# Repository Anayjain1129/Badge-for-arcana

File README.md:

# Badge-for-arcana
A PCB badge for horizons arcana! 

# Schematics 

# PCB

# Why did i made this?
I was just trying to try new projects and learn more about hardware projects.

# Features:-
- could be used as a arcana badge
- Awesome silkscreen
- uses 555 timer
- Cool Leds

# BOM 
| #  | Component                       |   Qty | Unit Price (USD) | Total (USD) |
| -- | ------------------------------- | ----: | ---------------: | ----------: |
| 1  | 555 Timer IC (NE555)            |     1 |            $0.20 |       $0.20 |
| 2  | CR2032 Coin Cell Battery        |     2 |            $0.35 |       $0.70 |
| 3  | CR2032 Coin Cell Battery Holder |     2 |            $0.15 |       $0.30 |
| 4  | 5mm LED                         |     6 |            $0.05 |       $0.30 |
| 5  | 270Ω Resistor                   |     6 |            $0.01 |       $0.06 |
| 6  | 10kΩ Resistor                   |     1 |            $0.01 |       $0.01 |
| 7  | 1kΩ Resistor                    |     1 |            $0.01 |       $0.01 |
| 8  | 100µF Capacitor                 |     1 |            $0.08 |       $0.08 |
| 9  | 6mm Push Button                 |     1 |            $0.05 |       $0.05 |
| 10 | **PCB**                         | **1** |        **$5.00** |   **$5.00** |
|    | **Total**                       |       |                  |   **$6.71** |

these components can be found easily in local market for cheaper prices!

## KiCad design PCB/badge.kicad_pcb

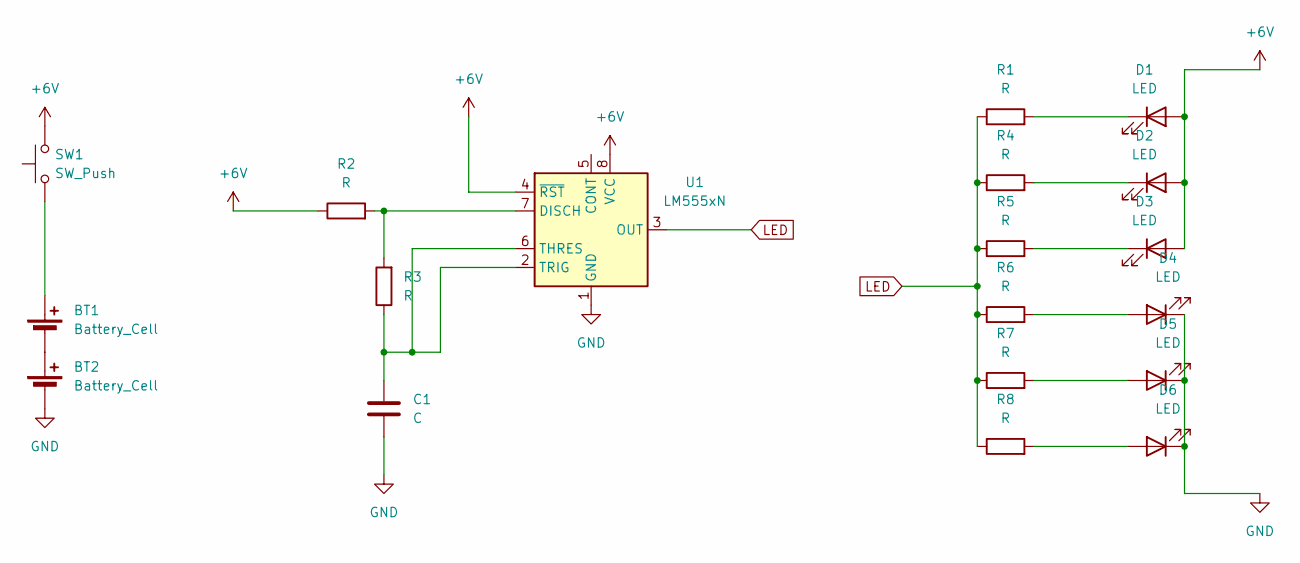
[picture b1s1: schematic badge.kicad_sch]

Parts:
BT1, BT2: Battery_Cell; BatteryHolder_MYOUNG_BS-07-A1BJ001_CR2032
C1: C; C_Radial_D6.3mm_H5.0mm_P2.50mm
D1, D2, D3, D4, D5, D6: LED; LED_D5.0mm
R1, R2, R3, R4, R5, R6, R7, R8: R; R_Axial_DIN0207_L6.3mm_D2.5mm_P7.62mm_Horizontal
SW1: SW_Push; SW_PUSH_6mm
U1: LM555xN; DIP-8_W7.62mm

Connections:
+6V: D1.2 (A), D2.2 (A), D3.2 (A), R2.1, SW1.2, U1.4 (~RST), U1.8 (VCC)
GND: BT2.2 (-), C1.2, D4.1 (K), D5.1 (K), D6.1 (K), U1.1 (GND)
LED: R1.1, R4.1, R5.1, R6.1, R7.1, R8.1, U1.3 (OUT)
unnamed: BT1.1 (+), SW1.1
unnamed: BT1.2 (-), BT2.1 (+)
unnamed: D1.1 (K), R1.2
unnamed: D2.1 (K), R4.2
unnamed: D3.1 (K), R5.2
unnamed: D4.2 (A), R6.2
unnamed: D5.2 (A), R7.2
unnamed: D6.2 (A), R8.2
unnamed: R2.2, R3.2, U1.7 (DISCH)
unnamed: C1.1, R3.1, U1.2 (TRIG), U1.6 (THRES)

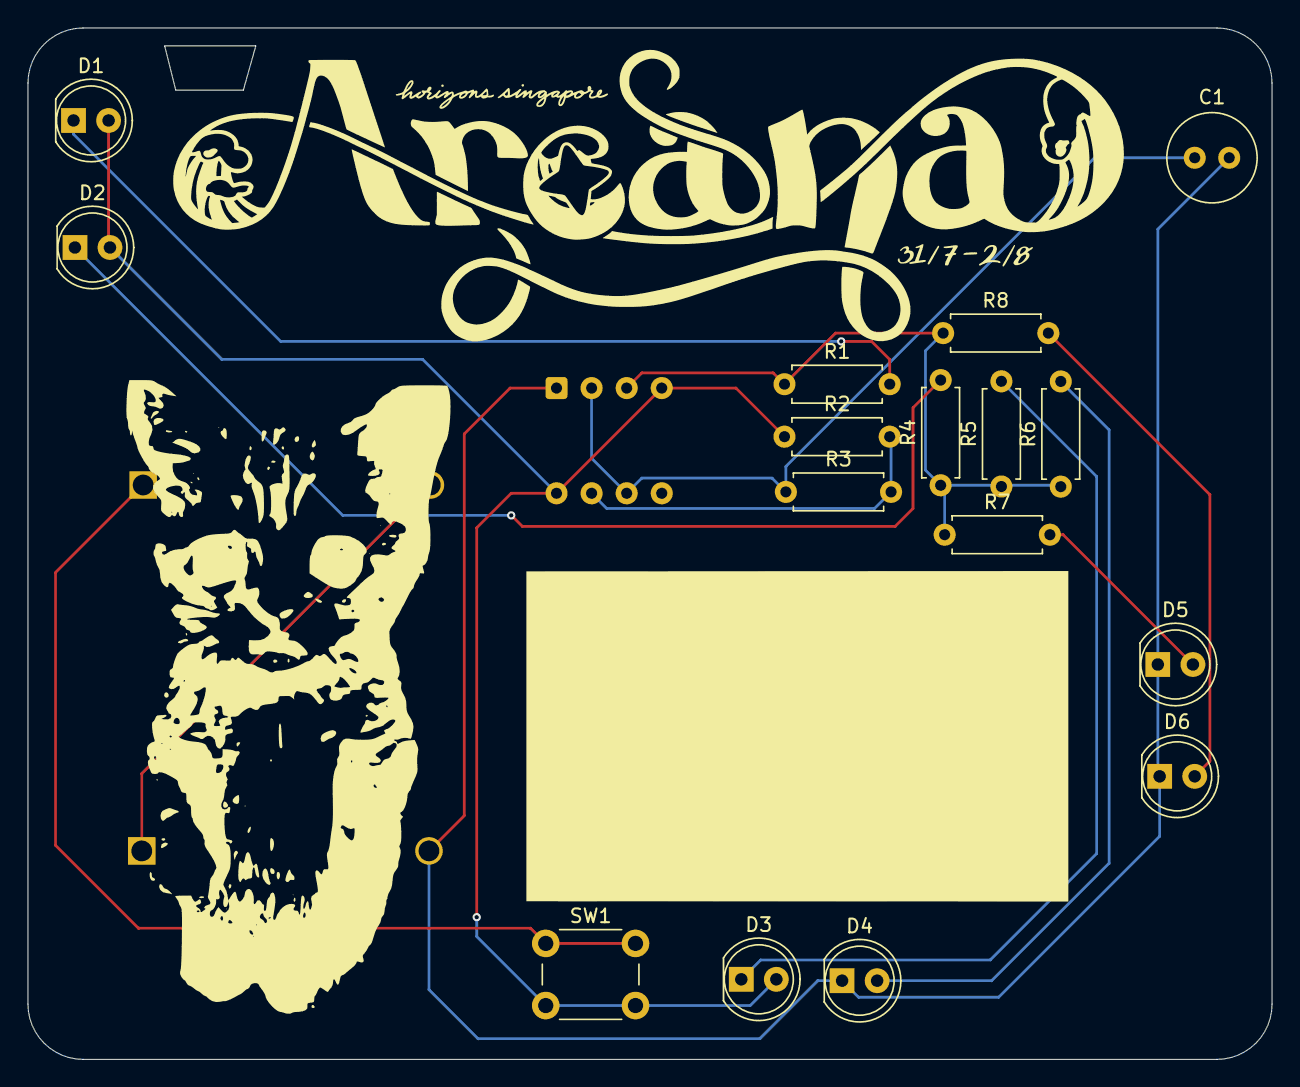
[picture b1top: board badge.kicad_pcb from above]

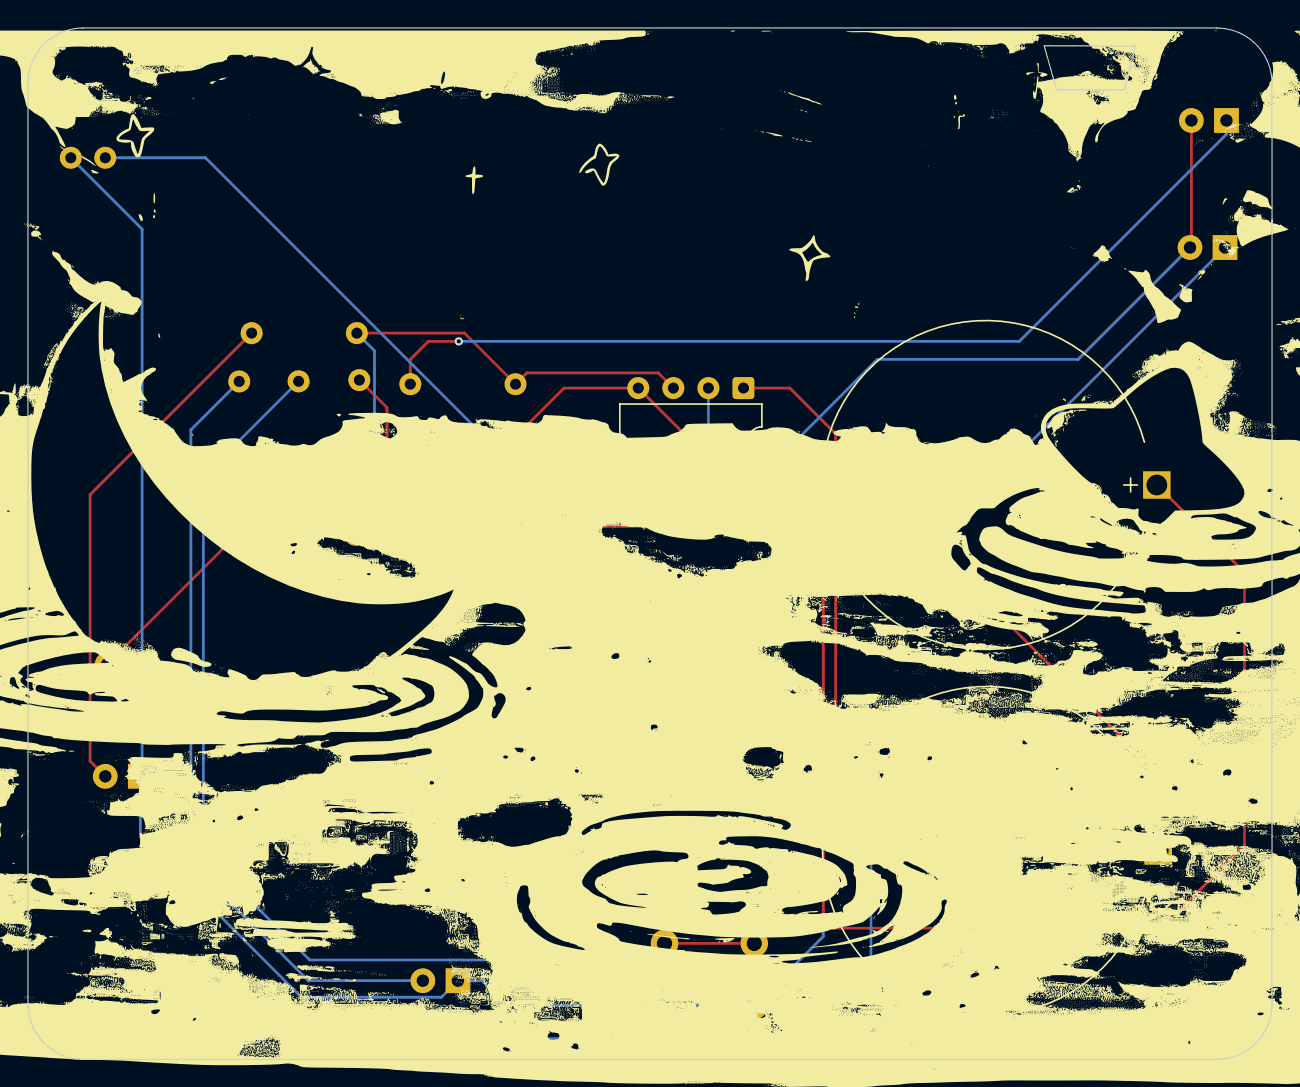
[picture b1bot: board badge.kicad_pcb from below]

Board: 2 copper layers, 90.1 x 74.7 mm, 19 parts (3 on the bottom side), 13 nets.
